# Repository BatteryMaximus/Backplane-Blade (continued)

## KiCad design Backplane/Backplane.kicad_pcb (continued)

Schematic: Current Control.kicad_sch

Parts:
C52, C53, C54, C55, C56, C57, C58: 100n; R_1206_3216Metric_Pad1.30x1.75mm_HandSolder
Q25, Q26: TPHR8504PL,LQ(M1W; DFN-5_L4.9-W5.9-P1.27-LS6.2-BL; LCSC Part C22388172
R122, R123: 10k; R_1206_3216Metric_Pad1.30x1.75mm_HandSolder
R124, R125, R126, R127, R128, R129, R132, R133: 1k; R_1206_3216Metric_Pad1.30x1.75mm_HandSolder
R130, R131: 100k; R_1206_3216Metric_Pad1.30x1.75mm_HandSolder
R134, R135: 0.003; R_1206_3216Metric_Pad1.30x1.75mm_HandSolder
U3: LM358; SOP-8_L4.9-W3.9-P1.27-LS6.0-BL
U28: LM393; SOP-8_L4.9-W3.9-P1.27-LS6.0-BL
U29: UCC27324DR; SOIC-8_L5.0-W4.0-P1.27-LS6.0-BL; LCSC Part C46427
U32, U33: MCP4725A0T-E/CH; SOT-23-6_L2.9-W1.6-P0.95-LS2.8-BL; LCSC Part C144198

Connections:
+3.3V: C55.1, C56.1, U32.3 (VDD), U33.3 (VDD); also elsewhere on the board
+12V: C52.1, C57.1, C58.1, U3.8 (V+), U28.8 (V+), U29.6 (VDD); also elsewhere on the board
/BatPair2/ADS1118/A2: R129.1; also elsewhere on the board
/BatPair2/ADS1119/A2: R128.1; also elsewhere on the board
/BatPair2/BAT_A_CC_SCL: U33.5 (SCL); also elsewhere on the board
/BatPair2/BAT_A_CC_SDA: U33.4 (SDA); also elsewhere on the board
/BatPair2/BAT_A_CHARGE: U29.2 (INA); also elsewhere on the board
/BatPair2/BAT_B_CC_SCL: U32.5 (SCL); also elsewhere on the board
/BatPair2/BAT_B_CC_SDA: U32.4 (SDA); also elsewhere on the board
/BatPair2/BAT_B_CHARGE: U29.4 (INB); also elsewhere on the board
/BatPair2/BatMax - Female1/P-: Q25.5 (D); also elsewhere on the board
/BatPair2/BatMax - Female/P-: Q26.5 (D); also elsewhere on the board
GND: C52.2, C53.1, C54.1, C55.2, C56.2, C57.2, C58.2, R132.2, R133.2, R134.2, R135.2, U3.4 (V-), U28.4 (V-), U29.3 (GND), U32.2 (VSS), U32.6 (A0), U33.2 (VSS), U33.6 (A0); also elsewhere on the board
unnamed: Q25.4 (G), R123.2, U28.7
unnamed: Q26.4 (G), R122.2, U28.1
unnamed: R124.2, R128.2, R130.1, U3.1
unnamed: R127.2, R129.2, R131.1, U3.7
unnamed: Q25.1 (S), Q25.2 (S), Q25.3 (S), R134.1, U3.3 (+)
unnamed: R130.2, R132.1, U3.2 (-)
unnamed: Q26.1 (S), Q26.2 (S), Q26.3 (S), R135.1, U3.5 (+)
unnamed: R131.2, R133.1, U3.6 (-)
unnamed: R126.1, U28.3 (+)
unnamed: R127.1, U28.2 (-)
unnamed: R125.1, U28.5 (+)
unnamed: R124.1, U28.6 (-)
unnamed: R122.1, U29.7 (OUTA)
unnamed: R123.1, U29.5 (OUTB)
unnamed: C53.2, R125.2, U32.1 (VOUT)
unnamed: C54.2, R126.2, U33.1 (VOUT)

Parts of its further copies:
C59, C60, C61, C62, C63, C64, C65: 100n; R_1206_3216Metric_Pad1.30x1.75mm_HandSolder
Q27, Q28: TPHR8504PL,LQ(M1W; DFN-5_L4.9-W5.9-P1.27-LS6.2-BL; LCSC Part C22388172
R136, R137: 10k; R_1206_3216Metric_Pad1.30x1.75mm_HandSolder
R138, R139, R140, R141, R142, R143, R146, R147: 1k; R_1206_3216Metric_Pad1.30x1.75mm_HandSolder
R144, R145: 100k; R_1206_3216Metric_Pad1.30x1.75mm_HandSolder
R148, R149: 0.003; R_1206_3216Metric_Pad1.30x1.75mm_HandSolder
U4: LM358; SOP-8_L4.9-W3.9-P1.27-LS6.0-BL
U34: LM393; SOP-8_L4.9-W3.9-P1.27-LS6.0-BL
U35: UCC27324DR; SOIC-8_L5.0-W4.0-P1.27-LS6.0-BL; LCSC Part C46427
U38, U39: MCP4725A0T-E/CH; SOT-23-6_L2.9-W1.6-P0.95-LS2.8-BL; LCSC Part C144198

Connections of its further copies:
+3.3V: C62.1, C63.1, U38.3 (VDD), U39.3 (VDD); also elsewhere on the board
+12V: C59.1, C64.1, C65.1, U4.8 (V+), U34.8 (V+), U35.6 (VDD); also elsewhere on the board
/BatPair1/ADS1118/A2: R143.1; also elsewhere on the board
/BatPair1/ADS1119/A2: R142.1; also elsewhere on the board
/BatPair1/BAT_A_CC_SCL: U39.5 (SCL); also elsewhere on the board
/BatPair1/BAT_A_CC_SDA: U39.4 (SDA); also elsewhere on the board
/BatPair1/BAT_A_CHARGE: U35.2 (INA); also elsewhere on the board
/BatPair1/BAT_B_CC_SCL: U38.5 (SCL); also elsewhere on the board
/BatPair1/BAT_B_CC_SDA: U38.4 (SDA); also elsewhere on the board
/BatPair1/BAT_B_CHARGE: U35.4 (INB); also elsewhere on the board
/BatPair1/BatMax - Female1/P-: Q27.5 (D); also elsewhere on the board
/BatPair1/BatMax - Female/P-: Q28.5 (D); also elsewhere on the board
GND: C59.2, C60.1, C61.1, C62.2, C63.2, C64.2, C65.2, R146.2, R147.2, R148.2, R149.2, U4.4 (V-), U34.4 (V-), U35.3 (GND), U38.2 (VSS), U38.6 (A0), U39.2 (VSS), U39.6 (A0); also elsewhere on the board
unnamed: Q27.4 (G), R137.2, U34.7
unnamed: Q28.4 (G), R136.2, U34.1
unnamed: R138.2, R142.2, R144.1, U4.1
unnamed: R141.2, R143.2, R145.1, U4.7
unnamed: Q27.1 (S), Q27.2 (S), Q27.3 (S), R148.1, U4.3 (+)
unnamed: R144.2, R146.1, U4.2 (-)
unnamed: Q28.1 (S), Q28.2 (S), Q28.3 (S), R149.1, U4.5 (+)
unnamed: R145.2, R147.1, U4.6 (-)
unnamed: R140.1, U34.3 (+)
unnamed: R141.1, U34.2 (-)
unnamed: R139.1, U34.5 (+)
unnamed: R138.1, U34.6 (-)
unnamed: R136.1, U35.7 (OUTA)
unnamed: R137.1, U35.5 (OUTB)
unnamed: C60.2, R139.2, U38.1 (VOUT)
unnamed: C61.2, R140.2, U39.1 (VOUT)

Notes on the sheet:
Gate Drive

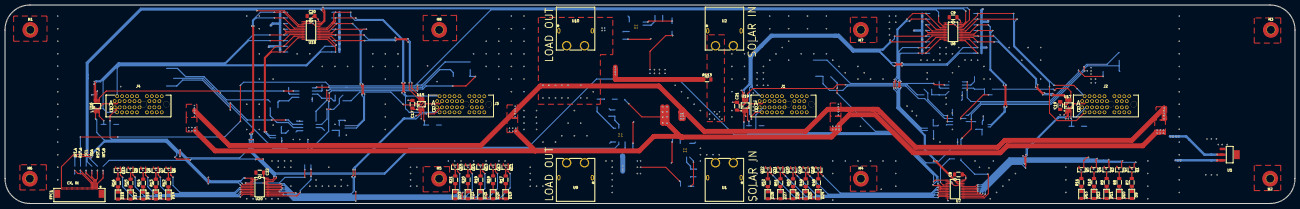
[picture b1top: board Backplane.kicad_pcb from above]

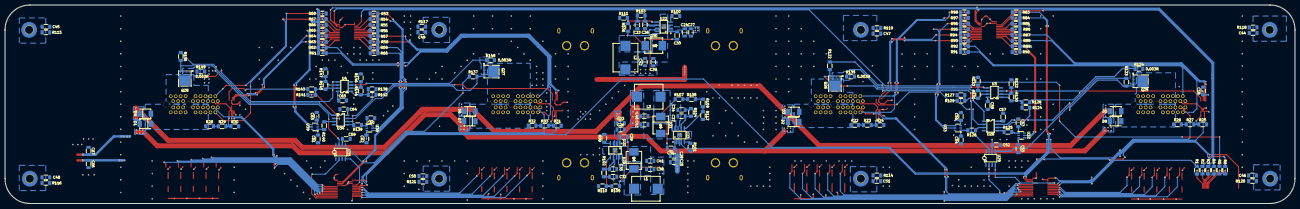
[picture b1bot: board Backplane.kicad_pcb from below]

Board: 6 copper layers, 520.0 x 80.0 mm, 271 parts (177 on the bottom side), 202 nets.

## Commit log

2025-03-31 First push.
2025-04-01 Starting to work on layout.
2025-04-03 Finished board layout.
2025-04-03 All parts are correct.
2025-04-03 Power supplies are layed out.
2025-04-03 Done with first I2CMux Layout.
2025-04-03 Finished with second I2C layout.
2025-04-03 EarthGround Done.
2025-04-03 First LED Bank Done.
2025-04-03 Done with layout for first current control
2025-04-03 Layout is almost done.
2025-04-04 Layout is done.
2025-04-04 Working on routing.
2025-04-04 Almost done routing signals.
2025-04-05 Routing almost done.
2025-04-06 Working on Power Zones
2025-04-06 First draft routing done.
2025-04-06 Finished routing.
2025-04-08 Added production files.
2025-06-17 added
